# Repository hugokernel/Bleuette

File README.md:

githubiverse-template
============

This project aims to produce a creature with 6 legs and must run without anyone's help.

Some of you may be familiar with the late 90’s tv show “F/X” where the main character (working with special effect) was getting the help of a small but smart robot named “Bleuet” (in French). This show sparkled the idea of creating a matte for Bleuet, that will be called “Bleuette”.

See the announcement of the resumption of development: http://www.digitalspirit.org/blog/index.php/post/2012/08/06/Le-retour-de-l-hexapode-Bleuette

More information in french : http://www.digitalspirit.org/wiki/index.php/Bleuette

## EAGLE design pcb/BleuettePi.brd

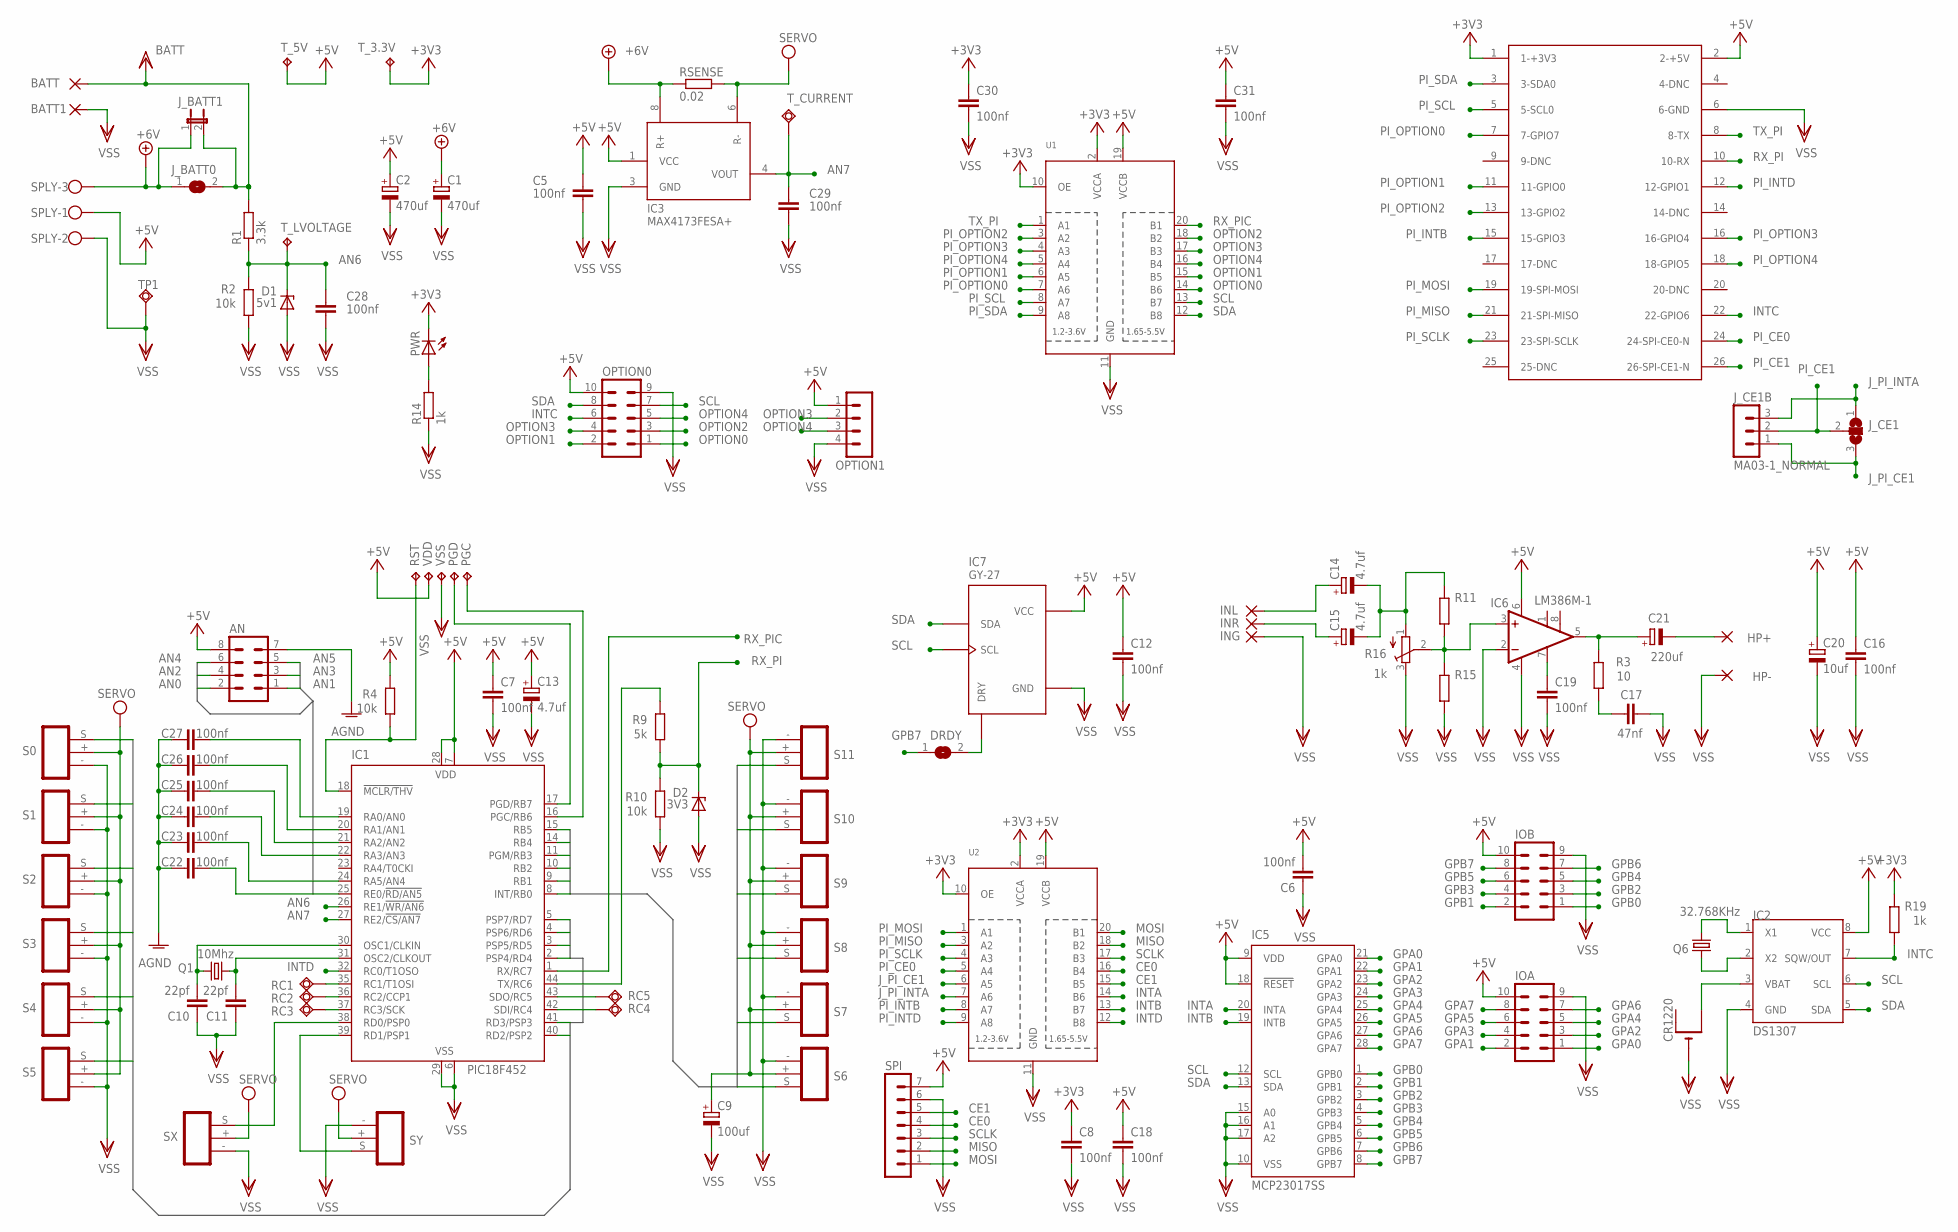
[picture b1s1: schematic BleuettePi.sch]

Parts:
AN: MA04-2
BATT, BATT1: 2,15/1,0
C1, C2: 470uf; PANASONIC_F
C5, C6, C7, C8, C12, C16, C18, C19, C22, C23, C24, C25, C26, C27, C28, C29, C30, C31: 100nf; C0805
C9: 100uf; PANASONIC_D
C10, C11: 22pf; C0805
C13, C14, C15: 4.7uf; CT3528
C17: 47nf; C0805
C20: 10uf; CT3528
C21: 220uf; PANASONIC_D
CR1220: CR1220THM; CR1220-THM
D1: 5v1; SOT23
D2: 3V3; SOT23
DRDY: SJ
HP+: 2,15/1,0
HP-: 2,15/1,0
IC1: PIC18F452; TQFP44
IC2: DS1307; SOIC-8
IC3: MAX4173FESA+; SO08
IC5: MCP23017SS; SSOP28
IC6: LM386M-1; SO08
IC7: GY-27
ING: 2,15/1,0
INL: 2,15/1,0
INR: 2,15/1,0
IOA: MA05-2
IOB: MA05-2
J_BATT0: SJ
J_BATT1: JP1E; JP1
J_CE1: SJ2W; SJ_2
J_CE1B: MA03-1_NORMAL
OPTION0: MA05-2
OPTION1: MA04-1
PGC: TPTP20R; TP20R
PGD: TPTP20R; TP20R
PWR: LEDCHIPLED_0805; CHIPLED_0805
Q1: 10Mhz; HC49UP@1
Q6: 32.768KHz; TC26H
R1: 3.3k; M0805
R2, R4, R10: 10k; M0805
R3: 10; M0805
R9: 5k; M0805
R11, R15: R-EU_M0805; M0805
R14, R19: 1k; M0805
R16: 1k; 3223J
RC1, RC2, RC3, RC4, RC5: TPSQTP06SQ; TP06SQ
RSENSE: 0.02; R4527
RST: TPTP20R; TP20R
S0, S1, S2, S3, S4, S5, S6, S7, S8, S9, S10, S11: CONN_SERVO
SPI: MA07-1
SPLY: W237-103
SX: CONN_SERVO
SY: CONN_SERVO
TP1: TPSQPAD1-13; P1-13
T_3.3V, T_5V: TPB1,27; B1,27
T_CURRENT: TPSQPAD1-13; P1-13
T_LVOLTAGE: TPB1,27; B1,27
U1, U2: TXB0108PWR; TSSOP20
U$3: RASPBERRY-PILIGHT-HOLE; RASPBERRY-PI-LIGHT-HOLE
VDD: TPTP20R; TP20R
VSS: TPTP20R; TP20R

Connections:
+3V3: C8.1, C30.1, PWR.C, R19.2, T_3.3V.TP, U1.2 (VCCA), U1.10 (OE), U2.2 (VCCA), U2.10 (OE), U$3.1 (1-+3V3)
+5V: AN.8, C2.+, C5.1, C6.2, C7.1, C12.1, C13.+, C16.1, C18.1, C20.+, C31.1, IC1.7 (VDD), IC1.28 (VDD), IC2.8 (VCC), IC3.1 (VCC), IC5.9 (VDD), IC5.18 (!RESET), IC6.6 (VS), IC7.VCC, IOA.10, IOB.10, OPTION0.10, OPTION1.1, R4.2, SPI.7, SPLY.1, T_5V.TP, U1.19 (VCCB), U2.19 (VCCB), U$3.2 (2-+5V), VDD.TP
+7V: C1.+, IC3.8 (R+), J_BATT0.1, J_BATT1.1, RSENSE.1, SPLY.3
AGND: AN.7, C22.1, C23.1, C24.1, C25.1, C26.1, C27.1
AN0: AN.2, C27.2, IC1.19 (RA0/AN0)
AN1: AN.1, C26.2, IC1.20 (RA1/AN1)
AN2: AN.4, C25.2, IC1.21 (RA2/AN2)
AN3: AN.3, C24.2, IC1.22 (RA3/AN3)
AN4: AN.6, C23.2, IC1.24 (RA5/AN4)
AN5: AN.5, C22.2, IC1.25 (RE0/!RD/AN5)
AN6: C28.2, D1.3 (C), IC1.26 (RE1/!WR/AN6), R1.1, R2.2, T_LVOLTAGE.TP
AN7: C29.2, IC1.27 (RE2/!CS/AN7), IC3.4 (VOUT), T_CURRENT.TP
CE0: SPI.4, U2.16 (B4)
CE1: SPI.5, U2.15 (B5)
GPA0: IC5.21 (GPA0), IOA.1
GPA1: IC5.22 (GPA1), IOA.2
GPA2: IC5.23 (GPA2), IOA.3
GPA3: IC5.24 (GPA3), IOA.4
GPA4: IC5.25 (GPA4), IOA.5
GPA5: IC5.26 (GPA5), IOA.6
GPA6: IC5.27 (GPA6), IOA.7
GPA7: IC5.28 (GPA7), IOA.8
GPB0: IC5.1 (GPB0), IOB.1
GPB1: IC5.2 (GPB1), IOB.2
GPB2: IC5.3 (GPB2), IOB.3
GPB3: IC5.4 (GPB3), IOB.4
GPB4: IC5.5 (GPB4), IOB.5
GPB5: IC5.6 (GPB5), IOB.6
GPB7: DRDY.1, IC5.8 (GPB7), IOB.8
INTA: IC5.20 (INTA), U2.14 (B6)
INTB: IC5.19 (INTB), U2.13 (B7)
INTC: IC2.7 (SQW/OUT), OPTION0.6, R19.1, U$3.22 (22-GPIO6)
INTD: IC1.32 (RC0/T1OSO), U2.12 (B8)
J_PI_CE1: J_CE1.3, J_CE1B.1, U2.6 (A5)
J_PI_INTA: J_CE1.1, J_CE1B.3, U2.7 (A6)
MISO: SPI.2, U2.18 (B2)
MOSI: SPI.1, U2.20 (B1)
unnamed 37: C11.2, IC1.31 (OSC2/CLKOUT), Q1.1; also elsewhere on the board
unnamed 38: C10.2, IC1.30 (OSC1/CLKIN), Q1.2; also elsewhere on the board
unnamed: C14.-, C15.-, R11.2, R16.1 (A)
unnamed: C14.+, INL.1
unnamed: C21.-, HP+.1
unnamed: IC1.38 (RD0/PSP0), SX.S
unnamed: IC1.17 (PGD/RB7), PGD.TP
unnamed: IC1.16 (PGC/RB6), PGC.TP
unnamed: IC1.39 (RD1/PSP1), SY.S
unnamed: IC2.1 (X1), Q6.2
unnamed: IC2.2 (X2), Q6.1
unnamed: DRDY.2, IC7.DRY
unnamed: PWR.A, R14.2
unnamed: C15.+, INR.1
unnamed: IC6.3 (+IN), R11.1, R15.2, R16.2 (S)
unnamed: C21.+, IC6.5 (OUT), R3.2
unnamed: C17.1, R3.1
unnamed: C19.1, IC6.7 (BYPASS)
unnamed: CR1220.+2 (+1), IC2.3 (VBAT)
OPTION0: OPTION0.1, U1.14 (B6)
OPTION1: OPTION0.2, U1.15 (B5)
OPTION2: OPTION0.3, U1.18 (B2)
OPTION3: OPTION0.4, OPTION1.2, U1.17 (B3)
OPTION4: OPTION0.5, OPTION1.3, U1.16 (B4)
PI_CE0: U2.5 (A4), U$3.24 (24-SPI-CE0-N)
PI_CE1: J_CE1.2, J_CE1B.2, U$3.26 (26-SPI-CE1-N)
PI_INTB: U2.8 (A7), U$3.15 (15-GPIO3)
PI_INTD: U2.9 (A8), U$3.12 (12-GPIO1)
PI_MISO: U2.3 (A2), U$3.21 (21-SPI-MISO)
PI_MOSI: U2.1 (A1), U$3.19 (19-SPI-MOSI)
PI_OPTION0: U1.7 (A6), U$3.7 (7-GPIO7)
PI_OPTION1: U1.6 (A5), U$3.11 (11-GPIO0)
PI_OPTION2: U1.3 (A2), U$3.13 (13-GPIO2)
PI_OPTION3: U1.4 (A3), U$3.16 (16-GPIO4)
PI_OPTION4: U1.5 (A4), U$3.18 (18-GPIO5)
PI_SCL: U1.8 (A7), U$3.5 (5-SCL0)
PI_SCLK: U2.4 (A3), U$3.23 (23-SPI-SCLK)
PI_SDA: U1.9 (A8), U$3.3 (3-SDA0)
RC1: IC1.35 (RC1/T1OSI), RC1.TP
RC2: IC1.36 (RC2/CCP1), RC2.TP
RC5: IC1.43 (SDO/RC5), RC5.TP
RX_PI: D2.3 (C), R9.1, R10.2, U$3.10 (10-RX)
RX_PIC: IC1.1 (RX/RC7), U1.20 (B1)
SCLK: SPI.3, U2.17 (B3)
SS0: IC1.40 (RD2/PSP2), S0.S
SS1: IC1.41 (RD3/PSP3), S1.S
SS2: IC1.2 (PSP4/RD4), S2.S
SS3: IC1.3 (PSP5/RD5), S3.S
SS4: IC1.4 (PSP6/RD6), S4.S
SS5: IC1.5 (PSP7/RD7), S5.S
SS6: IC1.8 (INT/RB0), S6.S
SS7: IC1.9 (RB1), S7.S
SS8: IC1.10 (RB2), S8.S
SS9: IC1.11 (PGM/RB3), S9.S
SS10: IC1.14 (RB4), S10.S
SS11: IC1.15 (RB5), S11.S
TX_PI: U1.1 (A1), U$3.8 (8-TX)
TX_PIC: IC1.44 (TX/RC6), R9.2
VDD: BATT.1, J_BATT0.2, J_BATT1.2, R1.2
VEE: C9.+, IC3.6 (R-), RSENSE.2, S0.+, S1.+, S2.+, S3.+, S4.+, S5.+, S6.+, S7.+, S8.+, S9.+, S10.+, S11.+, SX.+, SY.+
VSS: BATT1.1, C1.-, C2.-, C5.2, C6.1, C7.2, C8.2, C9.-, C10.1, C11.1, C12.2, C13.-, C16.2, C17.2, C18.2, C19.2, C20.-, C28.1, C29.1, C30.2, C31.2, CR1220.-, D1.1 (A), D2.1 (A), HP-.1, IC1.6 (VSS), IC1.29 (VSS), IC2.4 (GND), IC3.3 (GND), IC5.10 (VSS), IC5.15 (A0), IC5.16 (A1), IC5.17 (A2), IC6.2 (-IN), IC6.4 (GND), IC7.GND, ING.1, IOA.9, IOB.9, OPTION0.9, OPTION1.4, R2.1, R10.1, R14.1, R15.1, R16.3 (E), S0.-, S1.-, S2.-, S3.-, S4.-, S5.-, S6.-, S7.-, S8.-, S9.-, S10.-, S11.-, SPI.6, SPLY.2, SX.-, SY.-, TP1.TP, U1.11 (GND), U2.11 (GND), U$3.6 (6-GND), VSS.TP; also elsewhere on the board

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
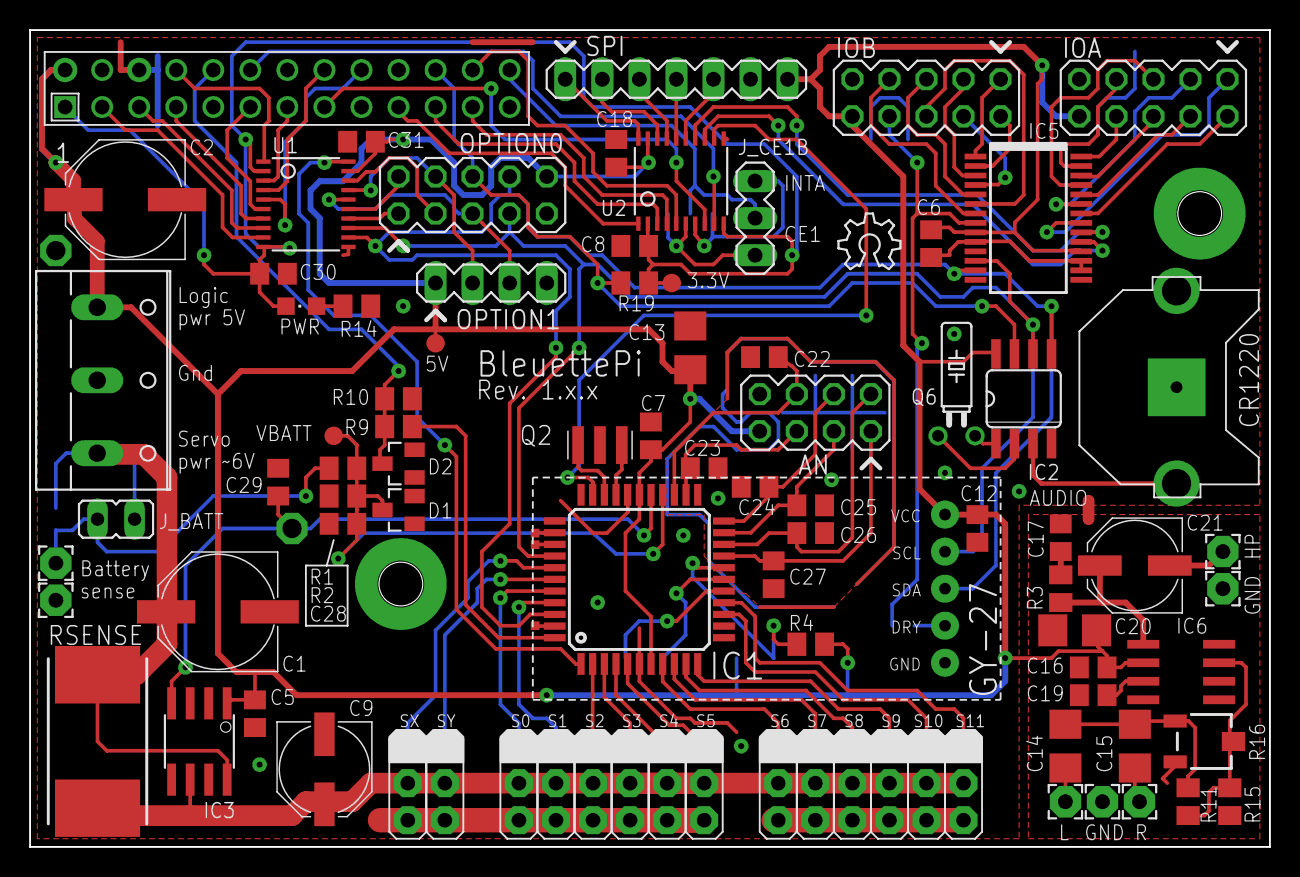
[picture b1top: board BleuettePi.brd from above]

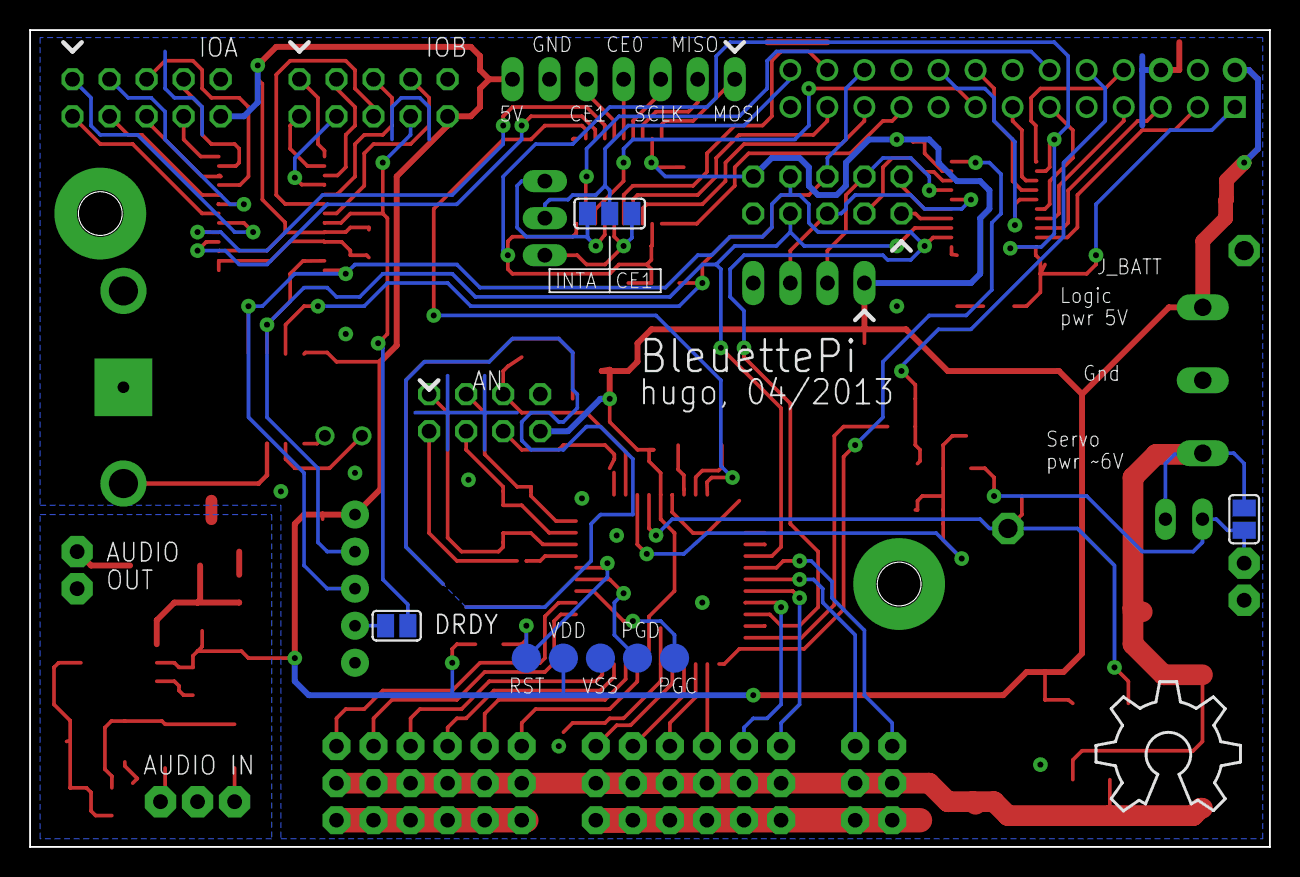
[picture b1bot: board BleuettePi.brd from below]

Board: 2 copper layers, 85.0 x 56.0 mm, 102 parts (9 on the bottom side), 101 nets.

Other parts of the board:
Q2: 10Mhz; CSTCR6M
U$2: OSHW_8X350_NOTEXT
U$5: OSHW_6X150_NOTEXT

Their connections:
unnamed 37: Q2.3; also elsewhere on the board
unnamed 38: Q2.1; also elsewhere on the board
VSS: Q2.2; also elsewhere on the board

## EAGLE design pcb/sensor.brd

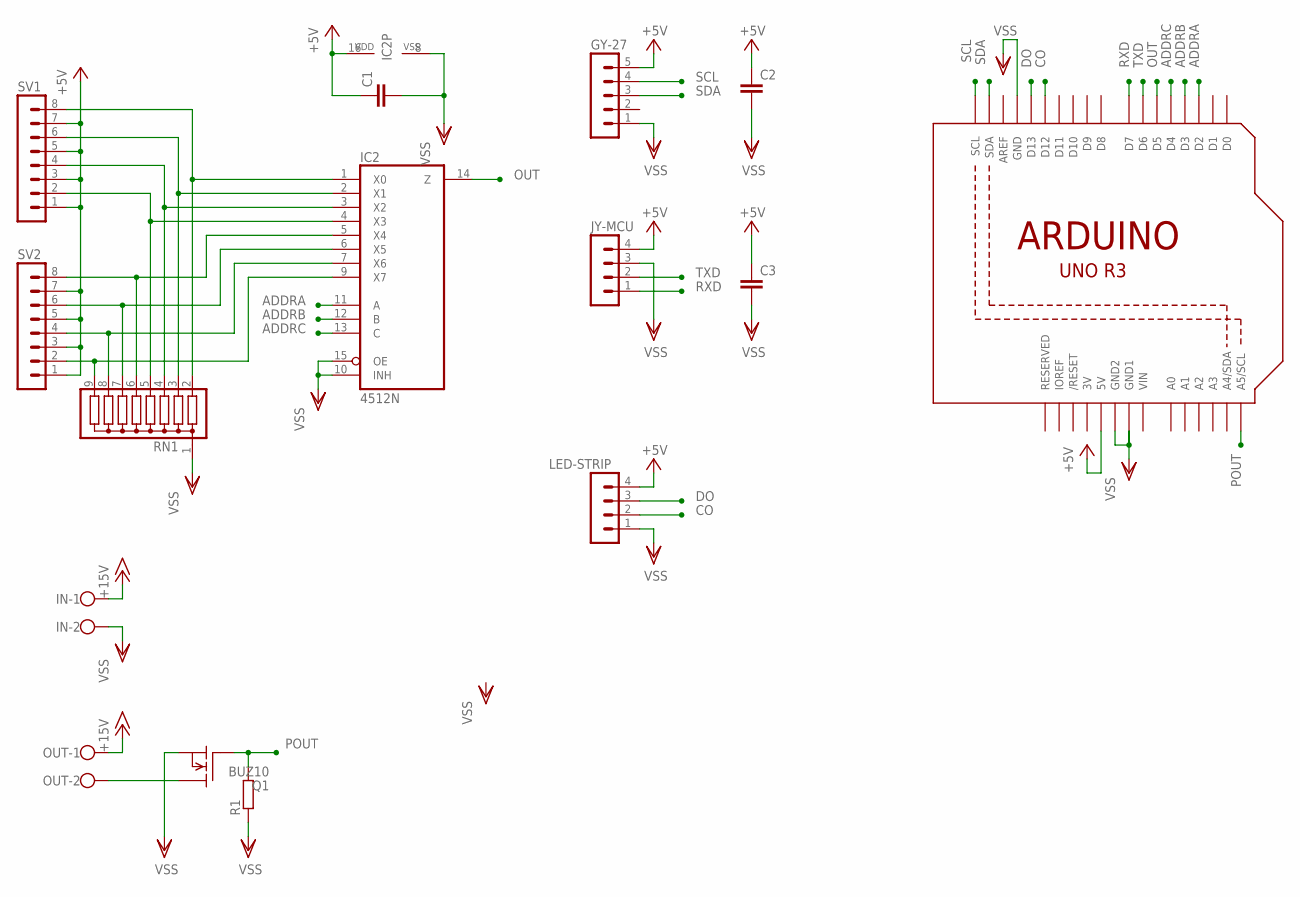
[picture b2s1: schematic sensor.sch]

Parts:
C1, C2, C3: C-EUC0805; C0805
GY-27: MA05-1
IC2: 4512N; DIL16
IN: W237-102
JY-MCU: MA04-1
LED-STRIP: MA04-1
OUT: W237-102
Q1: BUZ10; TO220
R1: R-EU_M0805; M0805
RN1: G08R; SIL9
SV1, SV2: MA08-1W
U1: ARDUINOR3-DIMENSION; ARDUINOR3

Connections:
3V: U1.3V
+5V: C1.1, C2.1, C3.1, GY-27.5, IC2.16 (VDD), JY-MCU.4, LED-STRIP.4, SV1.1, SV1.3, SV1.5, SV1.7, SV2.1, SV2.3, SV2.5, SV2.7, U1.5V
+15V: IN.1, OUT.1
ADDRA: IC2.11 (A), U1.D2
ADDRB: IC2.12 (B), U1.D3
ADDRC: IC2.13 (C), U1.D4
CO: LED-STRIP.2, U1.D12
DO: LED-STRIP.3, U1.D13
unnamed: IC2.5 (X4), RN1.6, SV2.8
unnamed: IC2.4 (X3), RN1.5, SV1.2
unnamed: IC2.3 (X2), RN1.4, SV1.4
unnamed: IC2.6 (X5), RN1.7, SV2.6
unnamed: IC2.2 (X1), RN1.3, SV1.6
unnamed: IC2.1 (X0), RN1.2, SV1.8
unnamed: IC2.9 (X7), RN1.9, SV2.2
unnamed: IC2.7 (X6), RN1.8, SV2.4
unnamed: OUT.2, Q1.2 (D)
OUT: IC2.14 (Z), U1.D5
POUT: Q1.1 (G), R1.2, U1.A5 (A5/SCL)
RXD: JY-MCU.1, U1.D7
SCL: GY-27.4, U1.SCL
SDA: GY-27.3, U1.SDA
TXD: JY-MCU.2, U1.D6
VIN: U1.VIN
VSS: C1.2, C2.2, C3.2, GY-27.1, IC2.8 (VSS), IC2.10 (INH), IC2.15 (OE), IN.2, JY-MCU.3, LED-STRIP.1, Q1.3 (S), R1.1, RN1.1, U1.GND, U1.GND1, U1.GND2

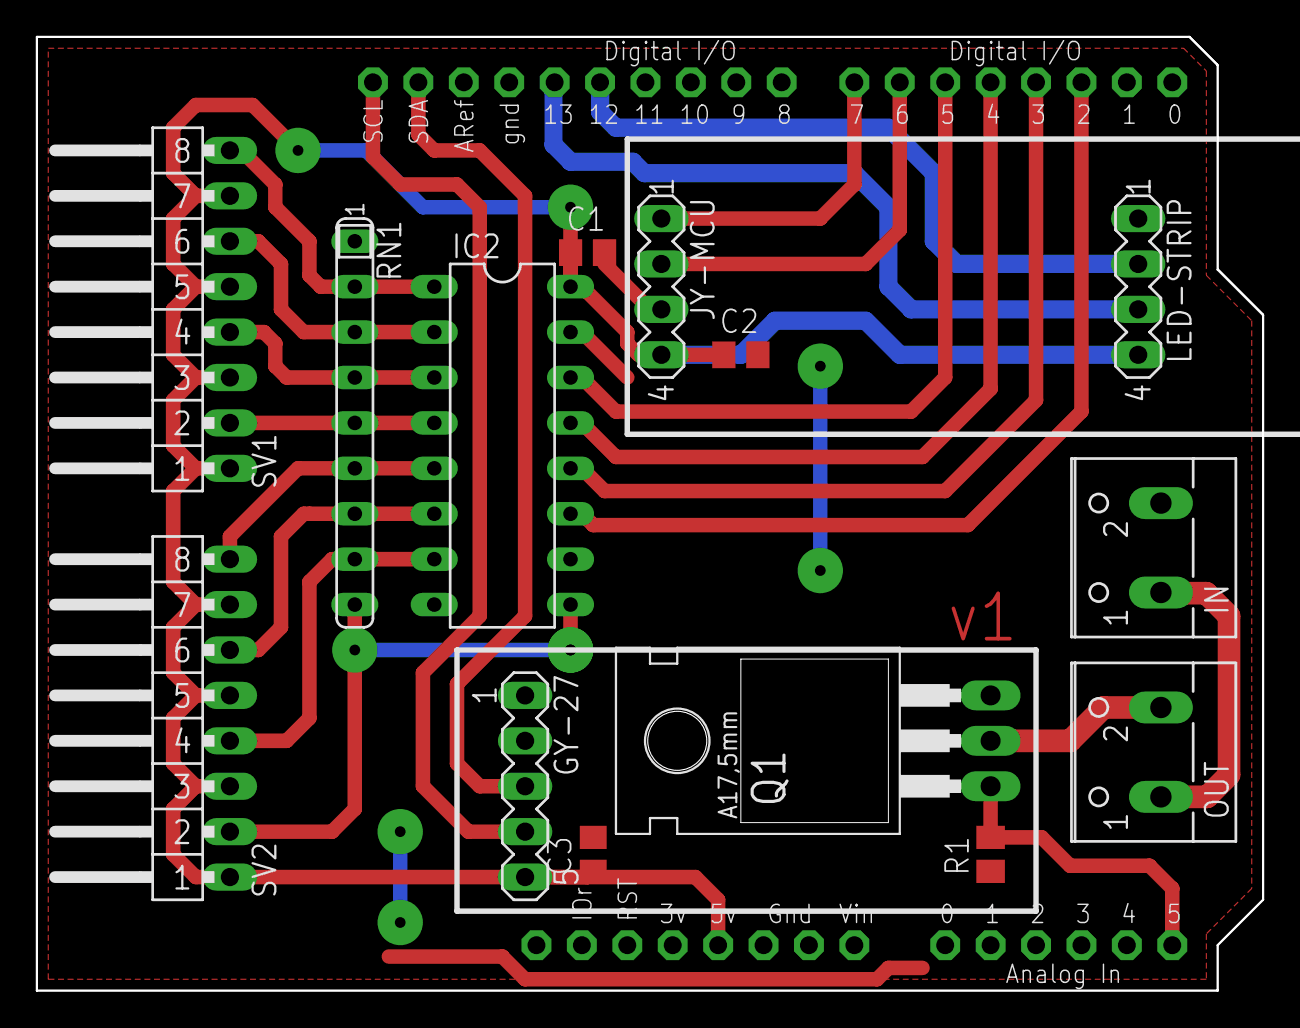
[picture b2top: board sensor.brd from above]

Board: 2 copper layers, 68.6 x 53.3 mm, 15 parts (0 on the bottom side), 23 nets.

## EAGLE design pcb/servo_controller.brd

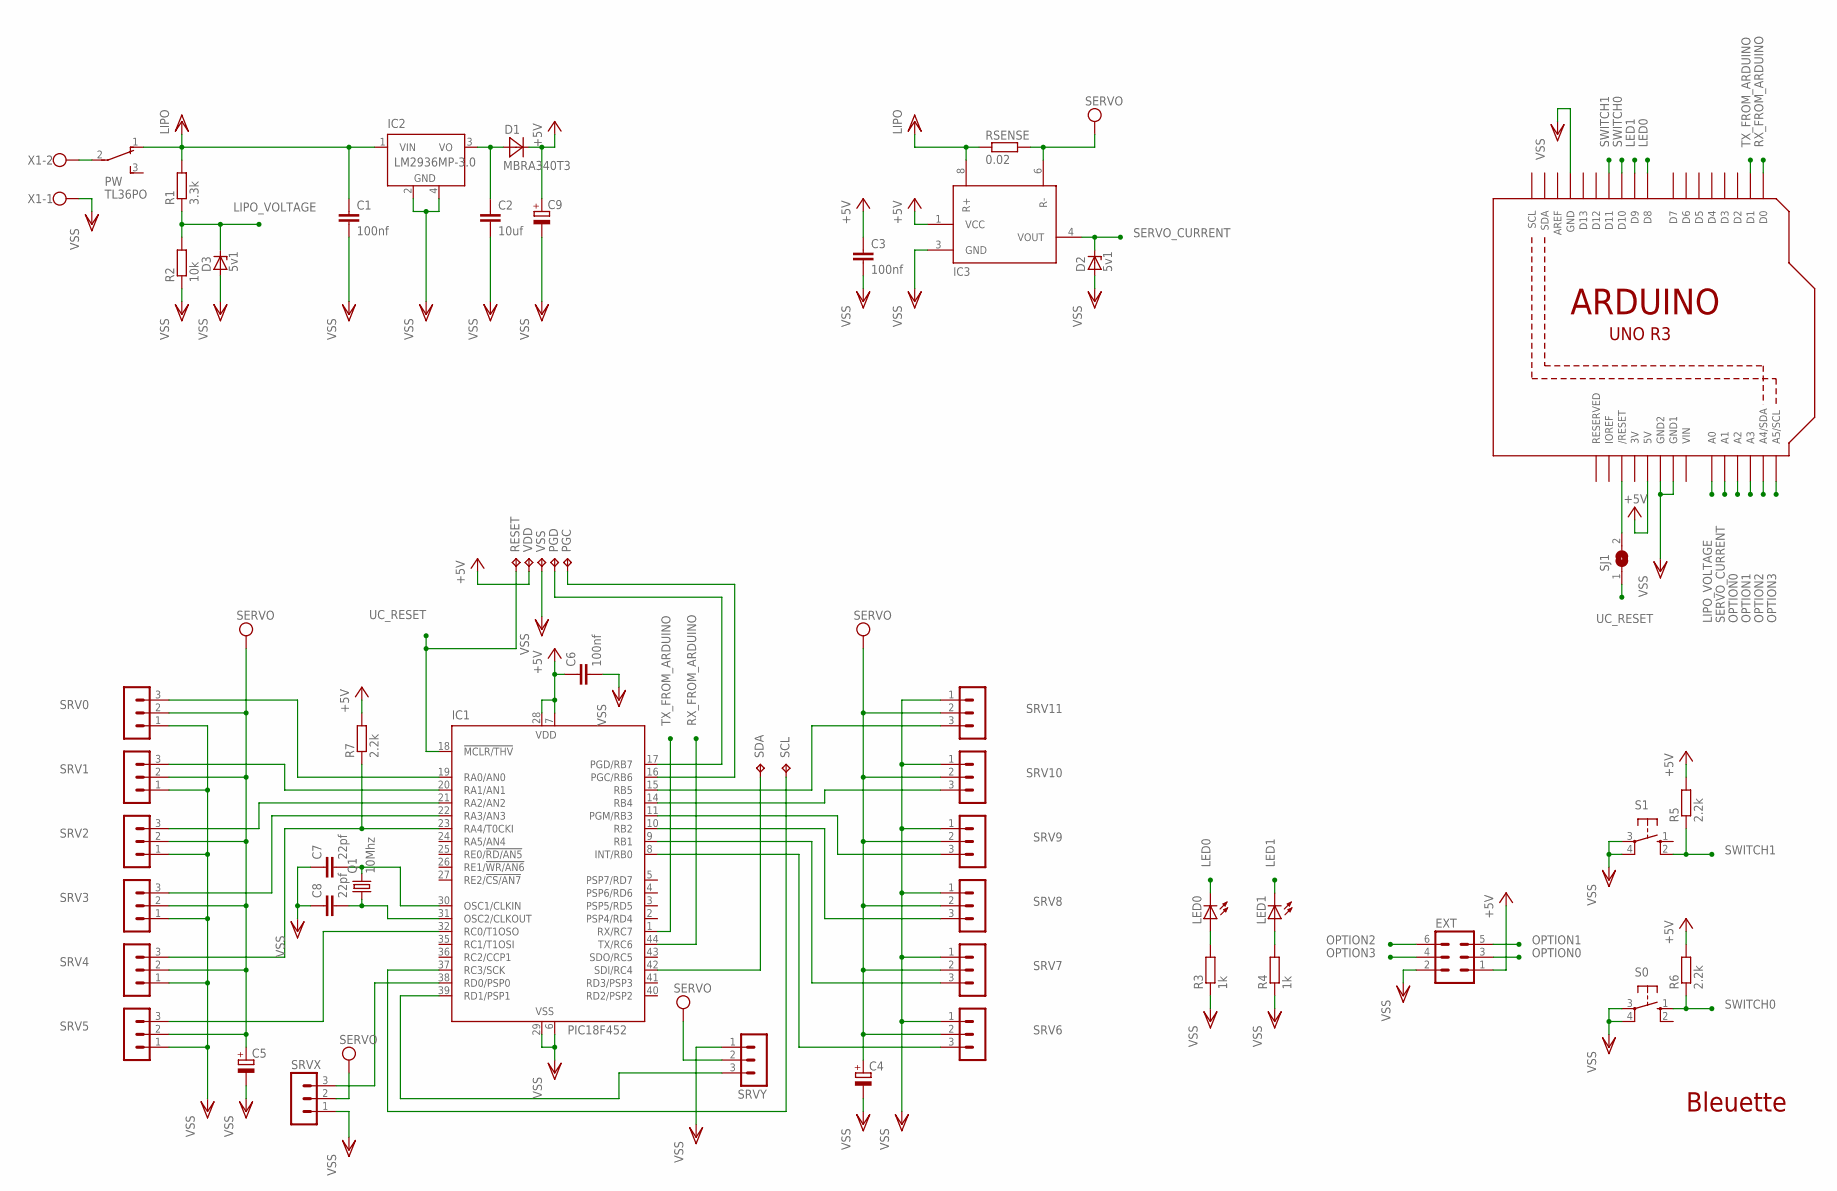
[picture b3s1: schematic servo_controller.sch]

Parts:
C1, C3, C6: 100nf; C1206
C2: 10uf; C1206
C4, C5: CPOL-EUD; PANASONIC_D
C7, C8: 22pf; C1206
C9: CPOL-EUF; PANASONIC_F
D1: MBRA340T3; SMA
D2, D3: 5v1; SOT23
EXT: MA03-2
IC1: PIC18F452; TQFP44
IC2: LM2936MP-3.0; SOT223
IC3: MAX4173A; SO08
LED0, LED1: LEDCHIPLED_0805; CHIPLED_0805
PGC: TPTP20R; TP20R
PGD: TPTP20R; TP20R
PW: TL36PO; TL3XPO
Q1: 10Mhz; HC49UP
R1: 3.3k; M1206
R2: 10k; M1206
R3, R4: 1k; M0805
R5, R6, R7: 2.2k; M0805
RESET: TPTP20R; TP20R
RSENSE: 0.02; R4527
S0, S1: 10-XX; B3F-10XX
SCL: TPTP20R; TP20R
SDA: TPTP20R; TP20R
SJ1: SJ
SRV0, SRV1, SRV2, SRV3, SRV4, SRV5, SRV6, SRV7, SRV8, SRV9, SRV10, SRV11: MA03-1
SRVX: MA03-1
SRVY: MA03-1
U1: ARDUINOR3-DIMENSION; ARDUINOR3
VDD: TPTP20R; TP20R
VSS: TPTP20R; TP20R
X1: W237-102

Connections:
3V: U1.3V
+5V: C3.1, C6.1, C9.+, D1.C, EXT.1, IC1.7 (VDD), IC1.28 (VDD), IC3.1 (VCC), R5.2, R6.2, R7.2, U1.5V, VDD.TP
LED0: LED0.C, U1.D8
LED1: LED1.C, U1.D9
LIPO_VOLTAGE: D3.3 (C), R1.1, R2.2, U1.A0
unnamed: IC1.19 (RA0/AN0), SRV0.3
unnamed: IC1.20 (RA1/AN1), SRV1.3
unnamed: IC1.21 (RA2/AN2), SRV2.3
unnamed: IC1.22 (RA3/AN3), SRV3.3
unnamed: IC1.23 (RA4/T0CKI), R7.1, SRV4.3
unnamed: IC1.32 (RC0/T1OSO), SRV5.3
unnamed: LED0.A, R3.2
unnamed: LED1.A, R4.2
unnamed: IC1.42 (SDI/RC4), SDA.TP
unnamed: IC1.8 (INT/RB0), SRV6.3
unnamed: IC1.9 (RB1), SRV7.3
unnamed: IC1.10 (RB2), SRV8.3
unnamed: IC1.11 (PGM/RB3), SRV9.3
unnamed: IC1.14 (RB4), SRV10.3
unnamed: PW.2, X1.2
unnamed: SJ1.2, U1.RESET (/RESET)
unnamed: IC1.37 (RC3/SCK), SCL.TP
unnamed: IC1.38 (RD0/PSP0), SRVX.3
unnamed: C2.1, D1.A, IC2.3 (VO)
unnamed: IC1.17 (PGD/RB7), PGD.TP
unnamed: IC1.16 (PGC/RB6), PGC.TP
unnamed: IC1.39 (RD1/PSP1), SRVY.3
unnamed: C8.2, IC1.31 (OSC2/CLKOUT), Q1.1
unnamed: C7.2, IC1.30 (OSC1/CLKIN), Q1.2
unnamed: IC1.15 (RB5), SRV11.3
OPTION0: EXT.3, U1.A2
OPTION1: EXT.5, U1.A3
OPTION2: EXT.6, U1.A4 (A4/SDA)
OPTION3: EXT.4, U1.A5 (A5/SCL)
RX_FROM_ARDUINO: IC1.44 (TX/RC6), U1.D0
SERVO_CURRENT: D2.3 (C), IC3.4 (VOUT), U1.A1
SWITCH0: R6.1, S0.1 (S), U1.D10
SWITCH1: R5.1, S1.2 (S1), U1.D11
TX_FROM_ARDUINO: IC1.1 (RX/RC7), U1.D1
UC_RESET: IC1.18 (!MCLR/THV), RESET.TP, SJ1.1
VDD: C1.1, IC2.1 (VIN), IC3.8 (R+), PW.1 (O), R1.2, RSENSE.1
VEE: C4.+, C5.+, IC3.6 (R-), RSENSE.2, SRV0.2, SRV1.2, SRV2.2, SRV3.2, SRV4.2, SRV5.2, SRV6.2, SRV7.2, SRV8.2, SRV9.2, SRV10.2, SRV11.2, SRVX.2, SRVY.2
VIN: U1.VIN
VSS: C1.2, C2.2, C3.2, C4.-, C5.-, C6.2, C7.1, C8.1, C9.-, D2.1 (A), D3.1 (A), EXT.2, IC1.6 (VSS), IC1.29 (VSS), IC2.2 (GND), IC2.4 (GND), IC3.3 (GND), R2.1, R3.1, R4.1, S0.3, S0.4 (P1), S1.3, S1.4 (P1), SRV0.1, SRV1.1, SRV2.1, SRV3.1, SRV4.1, SRV5.1, SRV6.1, SRV7.1, SRV8.1, SRV9.1, SRV10.1, SRV11.1, SRVX.1, SRVY.1, U1.GND, U1.GND1, U1.GND2, VSS.TP, X1.1

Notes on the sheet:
Bleuette

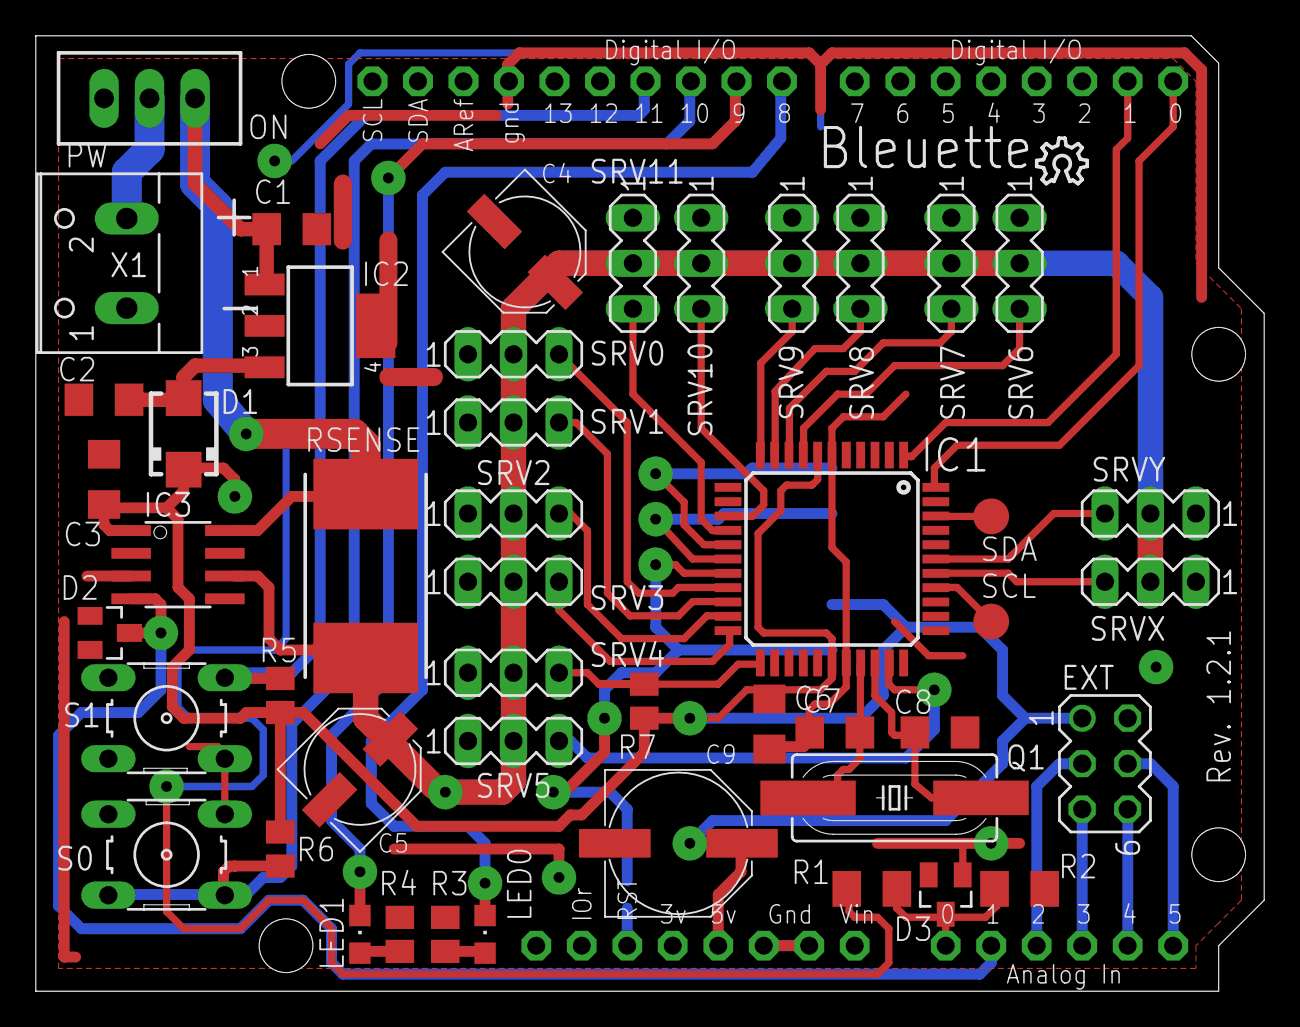
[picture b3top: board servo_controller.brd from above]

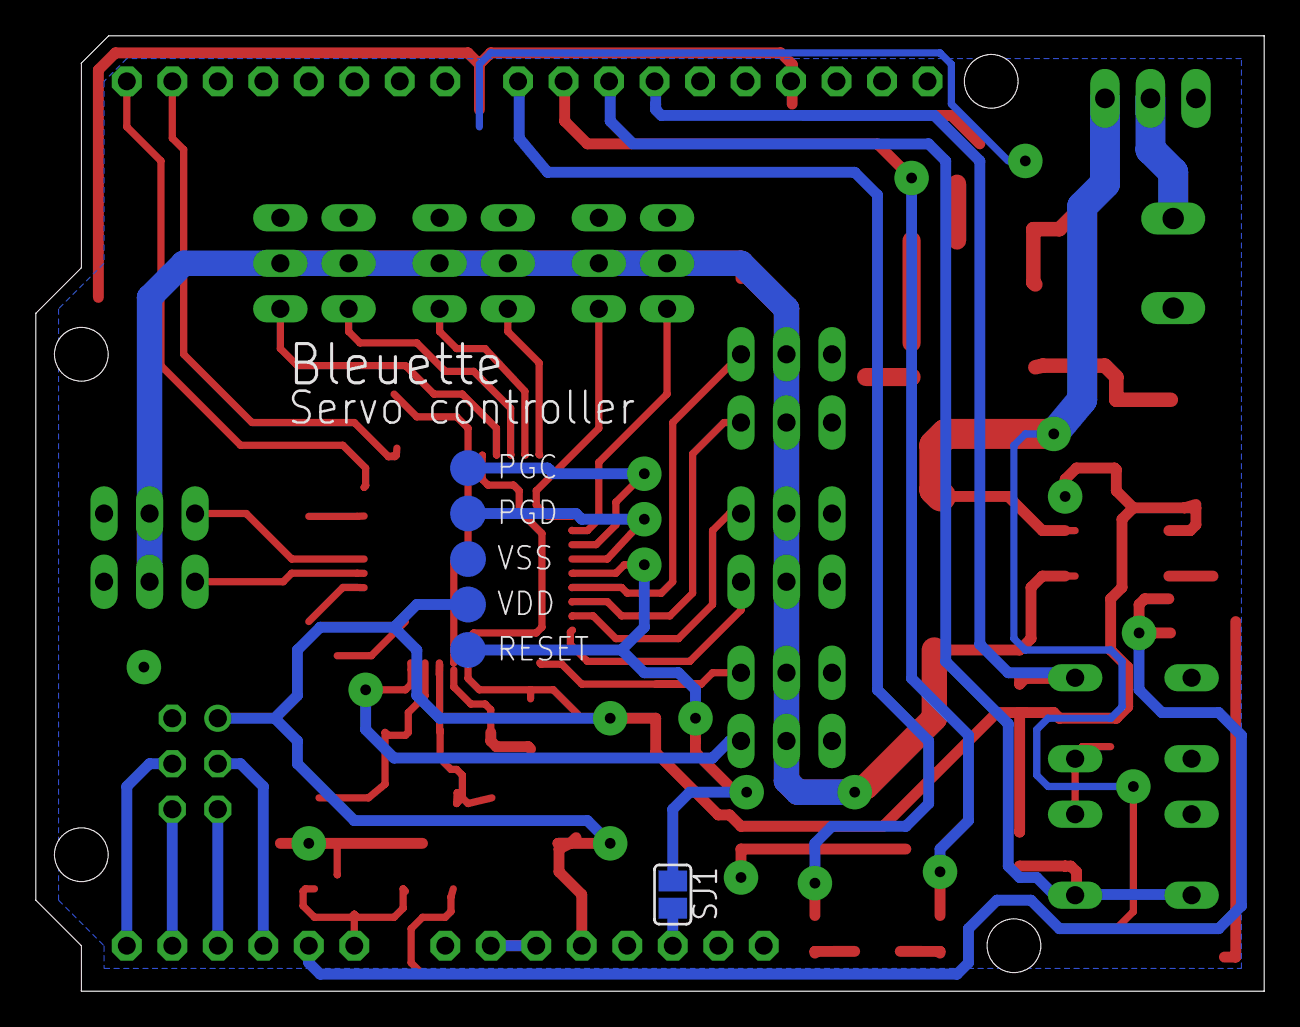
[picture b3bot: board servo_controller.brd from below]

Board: 2 copper layers, 68.6 x 53.3 mm, 55 parts (6 on the bottom side), 42 nets.

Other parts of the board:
U$1: OSHW_8X100_NOTEXT

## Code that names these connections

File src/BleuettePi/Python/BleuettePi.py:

#!/usr/bin/python
import serial, types, time, struct
from array import array

from Serial import Serial
from Servo import Servo
from Analog import Analog
import RPi.GPIO as GPIO

'''
import threading, copy
class MyThread ( threading.Thread ):

    def run ( self ):
        time.sleep(5)
        print 'Done'
'''

class BleuettePi:

    INTA = 26
    INTB = 15
    INTC = 22
    INTD = 12

    ser = None

    def __init__(self, mixed):
        self.com = Serial().connect(mixed)

        self.Servo = Servo(self.com)
        self.Analog = Analog(self.com)

        # Init mode
        GPIO.setmode(GPIO.BOARD)

        GPIO.setup(self.INTA, GPIO.IN)
        GPIO.setup(self.INTB, GPIO.IN)
        GPIO.setup(self.INTC, GPIO.IN)
        GPIO.setup(self.INTD, GPIO.IN)

        GPIO.add_event_detect(self.INTA, GPIO.RISING, callback = self.interrupt, bouncetime = 300)
        GPIO.add_event_detect(self.INTB, GPIO.RISING, callback = self.interrupt, bouncetime = 300)
        GPIO.add_event_detect(self.INTC, GPIO.RISING, callback = self.interrupt, bouncetime = 300)
        GPIO.add_event_detect(self.INTD, GPIO.RISING, callback = self.interrupt, bouncetime = 300)

        while True:
            time.sleep(20)

    def interrupt(self, index):
        if index == self.INTA:
            print "Interrupt from GPA"
        elif index == self.INTB:
            print "Interrupt from GPB"
        elif index == self.INTC:
            print "Interrupt from RTC"
        elif index == self.INTD:
            print "Interrupt from PIC !"
            print self.Analog.status()

    def getCurrent(self):
        total = 0;
        val = BPi.Analog.read(Analog.AN7)
        val += BPi.Analog.read(Analog.AN7)
        val += BPi.Analog.read(Analog.AN7)
        val += BPi.Analog.read(Analog.AN7)
        val += BPi.Analog.read(Analog.AN7)
        return val / 5

class Fake:
    @staticmethod
    def write(self):
        pass
    @staticmethod
    def read(self):
        pass

if __name__ == '__main__':

    BPi = BleuettePi('/dev/ttyAMA0')
    #BPi = BleuettePi(Fake)

    val = BPi.Analog.status()
    val = BPi.Analog.read(Analog.AN0)
    print BPi.Analog.convertInVolt(val)

    '''
    print "Current:", BPi.Analog.convertInVolt(BPi.Analog.readCurrent())

    value = chr(50)
    BPi.Servo.setValue(5, value)
    BPi.Servo.setValue(4, value)
    BPi.Servo.setValue(3, value)
#    BPi.Servo.setValue(13, chr(5))
    #BPi.Servo.setValue(5, chr(1))
    BPi.Servo.sendValues()
    '''

    print "Current:", BPi.Analog.convertInVolt(BPi.Analog.readCurrent())

    #while True:
    #    print BPi.getCurrent()
    #    time.sleep(1)

    #print BPi.monitor()

'''
    print "Set pos"
    BPi.Servo.setValues(Servo._2 | Servo._4, [ chr(90), chr(120) ])
    BPi.Servo.sendValues()
    #BPi.Servo.clear()
    #BPi.Servo.dump()

    time.sleep(2)

    print "Next"
    BPi.Servo.setValues(Servo._2 | Servo._4, [ chr(200), chr(20) ])
    BPi.Servo.sendValues()

#BleuettePi.Servo.sendValues()
#BleuettePi.ADC.get(0)
'''
'''
    MyThread().start()

BleuettePi
- Servos
- ADC 6 + 2
- GY-27
- Interruption
- 16 IO

 +-> BleuettePi
   +-> Serial
     +-> Servo
     +-> ADC
   +-> I2C
     +-> GY-27
     +-> IO
     +-> RTC
   +-> IO
     +-> Io / Interruption

'''

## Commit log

2012-07-09 Nouveau dépôt !
2012-07-10 Body
    Le corp de Bleuette !!
2012-07-11 Ajout du corp et des supports
2012-07-13 Cutter
2012-07-15 modif
2012-07-16 Cutter improvment
2012-07-25 New support holder with dovetail + hole
2012-07-25 Dovetail test
2012-07-26 Dovetail done !
2012-07-26 Bleuette cut ok !
2012-07-29 little mod
2012-07-30 Head screw
2012-07-30 Clean
2012-07-31 Servo hole, nut holder + cleanup
2012-07-31 Body threaded rod
2012-07-31 Complete demo
2012-07-31 Remove old leg connection
2012-07-31 Demo
2012-08-01 Threaded rod
2012-08-01 Added screw
2012-08-01 Servo position with hole
2012-08-01 Servo nut / screw + Arduino
2012-08-02 Clearance
2012-08-02 Add print test file
2012-08-02 Color servo !
2012-08-02 Clean, Doc
2012-08-02 Leg holder nut
2012-08-02 Misc
2012-08-02 Correct dimension
2012-08-03 Improve dimension
2012-08-03 Test
2012-08-04 Oblong
2012-08-04 Dimension
2012-08-04 openhardware logo + misc
2012-08-06 Leg holder placement correction
2012-08-06 Head
2012-08-06 Toolbox support
2012-08-07 New symmetrical rudder holder
2012-08-07 Adjustement
2012-08-07 Rudder holder adjustment + Servo holder adjustment + Leg hole
2012-08-07 Adjustment
2012-08-07 Rudder dimension
2012-08-08 Toolbox support modification
2012-08-08 Toolbox support modification bis + hole for cable
2012-08-09 Leg > Spacer connection
2012-08-10 Leg spacer blocker
2012-08-10 New arm connection
2012-08-10 Misc improvment
2012-08-10 Dimension + Demo update
2012-08-15 Servo arm + Thickness bug correction
2012-08-15 backup
2012-08-16 Servo modification
2012-08-17 Leg spacer
2012-08-20 White leg
2012-08-20 Servo controller schema
2012-08-20 Board
2012-08-20 Test body cut
2012-08-21 Dev pcb
2012-09-26 Work
2012-09-27 Avancement carte électronique
2012-09-28 Avancement PCB
2012-09-28 Add body stl
2012-10-04 Pcb, encore !
2012-10-09 PCB + Leg spring
2012-10-09 Spring improvment
2012-10-09 Add spring library
2012-10-10 PCB Version 1.0.0
2012-10-10 PCB Version 1.0.1
2012-10-12 Add export
2012-10-12 Pcb delete
2012-10-12 Spring modification
2012-10-17 Add thumbs
2012-10-22 Image
2012-10-22 Logo OpenSource Hardware
2012-10-22 Image export
2012-10-27 Spring
2012-11-11 Test spring
2012-11-13 Spring & Spacer
2012-11-13 Spring & Spacer test
2012-11-14 Spacer adjustment
2012-11-19 Update img export
2012-11-19 STL export clean
2012-11-19 Leg small shorter modification
2012-11-19 Stl and img export
2012-11-26 Modif pcb
2012-11-27 Rev. 1.0.2, gerber file generation
2012-11-29 Add spring
2012-11-29 Move gerber file in export/gerber directory
2012-12-03 First code
2012-12-07 Servo driver
2012-12-10 Code
2012-12-11 Algo in progress
2012-12-14 Sequence src
2013-01-01 Set values
2013-01-11 Servo pic assembler
2013-01-14 Servo controller
2013-01-14 Arduino code
2013-01-17 Pic asm + Arduino code
2013-01-19 Code !!
2013-01-21 Clean up !
2013-01-24 New sequencer
2013-01-27 Code !
2013-01-29 Sensor
2013-01-29 Modif sphere
2013-01-30 Sequencer
2013-02-03 Leg sensor + elec
2013-02-03 leg sensor modif
2013-02-03 Leg sensor
2013-02-04 Foot
2013-02-04 Foot / sensor !!
2013-02-06 Rev 1.1.0
    - Added zener in analog paths (current / voltage)
    - C2 and C3 inversed
    - Gnd and Vss connected
    - Added resistor (R7) to RA4 (open collector)
    - Rsense value to 0.02Ω
2013-02-06 Rev 1.2.0
    - Added C9 for better 5V filter
    - Added reset jumper
    - Added OpenHardware logo
2013-02-06 Rename export
2013-02-06 Rev. 1.2.1
    - Change switch to 2.54mm one
2013-02-07 default value
2013-02-10 Added sot23 footprint for max4173
2013-02-11 Sensor board
2013-02-12 Sensor board modif
2013-02-15 Sensor board, simple face
2013-02-15 Sensor board v1
2013-02-17 Export gcode sensor board
2013-02-21 Sensor board + sensor handler in Ardino code
2013-02-25 Spacer main hole diameter adaptation
2013-02-25 Spacer nut diameter fix
2013-02-26 Leg sensor modification
2013-02-28 Ino !
2013-02-28 Ino modif
2013-03-01 Added led strip connector
2013-03-01 Elec
2013-03-01 Export elec img
2013-03-01 Elec export 1.2.1
2013-03-12 Pcb modification
2013-03-18 Raspberry Pi
2013-03-19 Raspberry Pi pcb version
2013-03-20 Schema Pi
2013-03-21 Raspberry Pi PCB
2013-03-23 Sensor board milling + Raspberry Pi update
2013-03-25 RaspPi Board
2013-03-26 Rapsberry Pi board
2013-03-28 Bleuette Pi
2013-03-28 BleuettePi
2013-03-31 RaspberryPi
2013-04-09 Commit before big modif !
2013-04-11 BleuettePi encore !
2013-04-17 BleuettePi : Add RTC Clock
2013-04-18 BleuettePi, modif ADC
2013-04-18 BleuettePi : ADC modif
2013-04-22 BleuettePi work !
2013-04-23 BleuettePi new modification
2013-04-24 BleuettePi routage
2013-04-25 Routage BleuettePi
2013-04-27 BleuettePi...
2013-05-16 BleuettePi Version 1.0.0
    Last modif + Clean
2013-06-06 Add PCB 1.0.2 pics
2013-06-29 First Python code
2013-06-29 Servocontroller adaptation
2013-06-29 Debug ServoController
2013-06-30 Servo controller dev
2013-06-30 Added R4, MCLR pullup
2013-07-01 Dev Python BleuettePi
2013-07-02 Remove error
2013-07-02 Modif PIC
2013-07-03 Dev BleuettePi protocol
2013-07-03 Dev Python protocol
2013-07-06 Dev Sequencer
2013-07-07 Dev drivers
2013-07-08 PCB: GY-27 remonté
2013-07-08 PCB: Inverse location of batt sense and power connector
2013-07-24 Cad modification
2013-07-24 I2C linked to Pic + Misc
2013-07-24 Modif code
2013-07-24 Fake mode
2013-07-25 Python
2013-07-26 Drive
2013-08-26 OpenSCAD : wifi + speaker holes
2013-09-01 Tornado modif
2013-09-01 Added Wifi dongle + Speaker
2013-09-02 Drive mode + Ws
2013-09-03 Drive mode
2013-09-04 Tornado
2013-09-08 WS modif
2013-09-11 Ws, Graph
2013-09-13 Modif Tornado
2013-09-13 Frontend modification
2013-09-17 Notify, trim, move
2013-09-25 Graph, js, etc...
2013-10-01 Misc Python
2013-10-03 Software speed
2013-10-08 Baudrate to 19200
2013-10-08 Servo speed test
2013-10-17 Debug servo speed
2013-10-24 Create gh-pages branch via GitHub
2013-10-24 First page
2014-12-27 Suppression pour voir
2014-12-27 Cette fois je me plante pas
